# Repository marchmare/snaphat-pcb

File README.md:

# 🌻 SnapHAT - PCB design

SnapHAT is an addon for RaspberryPi Zero 2 W serving as a handheld photo camera device.

This repository contains KiCad 9 design files for the PCBs of the SnapHAT device (rev.1.1).
The boards' layout is prepared to be compatible with JLCPCB standard 2-layer PCB quote.

> [!WARNING] 
> This repository is work in progress — core features are functional, but the PCB for this device is still evolving and some parts of the design are not yet behaving as I hoped.
> To avoid unnecessary hardware headaches, check [Troubleshooting and required reworks](#troubleshooting-and-required-reworks) section!

> [!TIP] 
> Python-based app for this camera can be found in **[this repository](https://github.com/marchmare/snaphat-sw)**.

### Table of contents:

* [Features](#features)
* [Repository structure](#repository-structure)
* [Bill of Materials](#bill-of-materials)
* [Wire harnesses](#wire-harnesses)
* [RaspberryPi header connection map](#raspberrypi-header-connection-map)
* [Troubleshooting and required reworks](#troubleshooting-and-required-reworks)

## Features

* 40-pin Raspberry Pi GPIO header for integration with RaspberryPi Zero 2 W
* 8-pin PH connector and mounting support for 320x240 Waveshare 18366 2.4" LCD TFT display
* Usable with ZeroCam OV5647 5MPx wide-angled 120° camera modules or same form-factor alternatives
* <del>1200mAh Li-Po battery support (30x40mm cell footprint, 2 pin PH connector), on-board battery charging (MCP73871) and power monitoring (INA219)</del>
* USB-C charging and OTG connector for RaspberryPi SD card access (USB 2.0)
* USB OTG pogo-pin breakout board as Raspberry Pi HAT, accessing USB singals through pogo-pins, connected to main board via 4pin FFC cable
* 8 tactile user interface buttons (navigation and shutter)
* LIS2DW12 motion sensor for providing image orientation metadata
* passive buzzer for audio feedback
* exposed debug UART pins
* flower testpads, because joy and whimsy is in demand

## Repository structure

```
.
├─ main_board/
│   ├─ docs/
│   ├─ *.kicad_pro, *.kicad_sch, *.kicad_pcb
│   └─ README.md
├─ usb_hat/
│   ├─ docs/
│   ├─ *.kicad_pro, *.kicad_sch, *.kicad_pcb
│   └─ README.md
├─ img/
└─README.md
```

This repository contains two KiCad projects for each board:

* [**main_board**](main_board/) - SnapHAT main board with RaspberryPi socket connector and all camera device peripherals
* [**USB HAT**](usb_hat/) - USB OTG pogo-pin breakout board

Each board directory contains:

* `*.kicad_pro`, `*.kicad_sch`, `*.kicad_pcb` - KiCad 9 design files
* `docs/` - documentation outputs generated from the KiCad files - you will find BOM in CSV format and schematic PDF in there

In the root directory:
* `img/` - rendered previews of the boards and other images used by READMEs

## Bill of Materials

You can find BOMs for each board as CSV file in their respective `docs/` directories.
BOMs list PCB components, wire harness components, fasteners as well as OTS modules required to assemble the whole device. 

While designing SnapHAT, Farnell and TME were mostly taken into consideration as part vendors, however some parts need to be sourced from elsewhere (this applies mostly to OTS modules). 

Estimated component cost of the whole device is approximately 114 USD.

## Wire harnesses

### Display wire harness

To connect the Waveshare 18366 2.4" LCD TFT Display, use an 8-pin JST-PH (2.0 mm pitch) wire harness.
**This is not a straight-through cable — pin numbering is reversed between connectors.**

Part numbers for building the harness are listed in the main board's BOM and appear in its KiCad schematics as well.

#### Pin mapping:

| SnapHAT J1 | Signal      | LCD PH connector |
|------------|-------------|------------------|
| 1          | `3V3 (VCC)` | 8                |
| 2          | `GND`       | 7                |
| 3          | `MOSI (DIN)`| 6                |
| 4          | `SCLK (CLK)`| 5                |
| 5          | `SPI_CS`    | 4                |
| 6          | `DC`        | 3                |
| 7          | `RST`       | 2                |
| 8          | `BL`        | 1                |

### USB HAT FFC cable

To connect SnapHAT's USB HAT, use 4 core (1.0 mm pitch) >50 mm FFC cable, with **opposite sided contacts**. Proposed part number for this cable is listed in the USB HAT's BOM and appear in its KiCad schematics as well.

SnapHAT and USB HAT both include FFC connectors with top-side contacts (SnapHAT: J6, USB HAT: J1). When plugged in, FFC stiffener should face the PCB on both ends.

#### Pin mapping:

| SnapHAT J6 | Signal        | USB HAT J1 |
|------------|---------------|------------|
| 1          | `VBUS`        | 1          |
| 2          | `USBC_DATA_N` | 2          |
| 3          | `USBC_DATA_P` | 3          |
| 4          | `GND`         | 4          |

## RaspberryPi header connection map

Below table describes connected RaspberryPi GPIO pins and their intended function.

| Pin function              | Signal name        | GPIO (BCM) | Pin    | Pin    | GPIO (BCM) | Signal name      | Pin function                   | 
| ------------------------- | ------------------ | ---------- | ------ | ------ | ---------- | ---------------- | ------------------------------ |
| 3.3V power rail           | `+3V3`             | -          | **1**  | **2**  | -          | `+5V0`           | 5V power rail                  |
| I2C data                  | `I2C_SDA`          | 2          | **3**  | **4**  | -          | `+5V0`           | 5V power rail                  |
| I2C clock                 | `I2C_SCL`          | 3          | **5**  | **6**  | -          | `GND`            | Ground                         |
| _Not connected_           | -                  | 4          | **7**  | **8**  | 14         | `RPI_UART_TX`    | Debug UART Transmit          |
| Ground                    | `GND`              | -          | **9**  | **10** | 15         | `RPI_UART_RX`    | Debug UART Receive             |
| Menu button               | `BTN_MENU`         | 17         | **11** | **12** | 18         | `BUZZER_SIGNAL`  | Buzzer PWM                     |
| A button                  | `BTN_A`            | 27         | **13** | **14** | -          | `GND`            | Ground                         |
| B button                  | `BTN_B`            | 22         | **15** | **16** | 23         | -                | _Not connected_                |
| 3.3V power rail           | `+3V3`             | -          | **17** | **18** | 24         | `DISPLAY_RST`    | Display reset                  |
| Display SPI MOSI          | `DISPLAY_MOSI`     | 10         | **19** | **20** | -          | `GND`            | Ground                         |
| _Not connected_           | -                  | 9          | **21** | **22** | 25         | `DISPLAY_DC`     | Display Data/Command         |
| Display SPI serial clock  | `DISPLAY_SPI_SCLK` | 11         | **23** | **24** | 8          | `DISPLAY_SPI_CS` | Display SPI chip select        |
| Ground                    | `GND`              | -          | **25** | **26** | 7          | -                | _Not connected_                |
| Down button               | `BTN_D`            | 0          | **27** | **28** | 1          | -                | _Not connected_                |
| Left button               | `BTN_L`            | 5          | **29** | **30** | -          | `GND`            | Ground                         |
| Right button              | `BTN_R`            | 6          | **31** | **32** | 12         | `DISPLAY_BL`     | Display backlight PWM          |
| Up button                 | `BTN_U`            | 13         | **33** | **34** | -          | `GND`            | Ground                         |
| Low battery indicator LED | `LED_LBO`          | 19         | **35** | **36** | 16         | `LED_SHUTTER`    | Shutter activity LED indicator |
| Shutter button            | `BTN_SHUTTER`      | 26         | **37** | **38** | 20         | `ACCEL_INT1`     | Motion sensor interrupt 1      |
| Ground                    | `GND`              | -          | **39** | **40** | 21         | `ACCEL_INT2`     | Motion sensor interrupt 2      |

## Troubleshooting and required reworks

This revision's battery circuit (protection, charger and 5V boost) is still botched. Aside from this, SnapHAT is operational if powered by an external stable 5V supply like PC USB port or powerbank.

To make SnapHAT work in this case, simply connect VBUS to 5V0 (you can solder a wire between corresponding testpads). Keep the SW9 switch off to disable the battery charger circuit and prevent charging indicators flickering.

If you wish to dwell deeper into what's currently wrong with this design, here are symptoms observed during bringup:

* no power sourced from battery:
    - battery protection dual MOSFET have wrong topology, skip populating battery protection components entirely and populate R22 and R23 0R resistors instead to connect battery directly to the rest of the circuit. Make sure you use battery with a PCM in this case! 
* RaspberryPi stuck in boot loop when powering from battery or weaker USB port:
    - battery charging/boost regulator circuit is still wrong in this iteration, for the time being, connect VBUS testpad with the 5V0 one
* SnapHAT gets powered from connected USB-C connector when USB HAT is installed, despite turning SW9 in off position:
    - cut the VBUS trace going to J6 pin 1

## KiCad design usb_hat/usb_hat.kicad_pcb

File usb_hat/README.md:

# SnapHAT USB HAT

This directory contains design files and documentation for SnapHAT USB HAT.

## Directory structure

```
.
└─ usb_hat/
   ├─ docs/
   │    ├─ *_bom.csv
   │    └─ *_schematic.pdf
   ├─ *.kicad_pro, *.kicad_sch, *.kicad_pcb
   └─ README.md
```

## Board previews

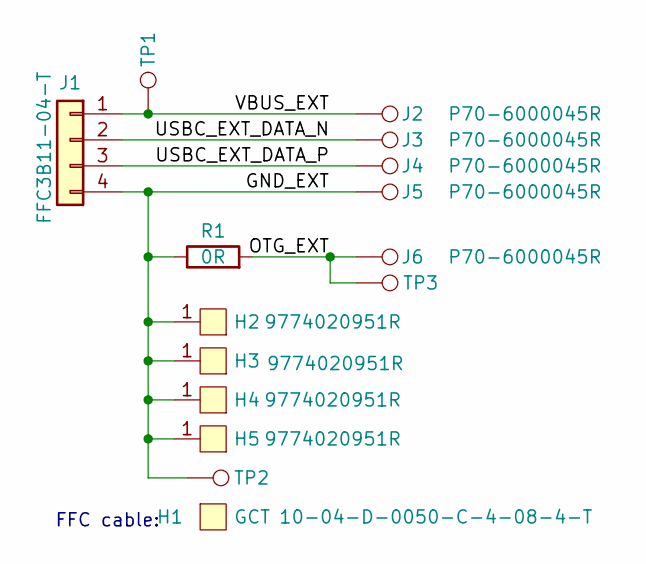
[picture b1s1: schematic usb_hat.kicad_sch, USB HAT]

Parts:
H1: 10-04-D-0050-C-4-08-4-T; Part number 10-04-D-0050-C-4-08-4-T
H2, H3, H4, H5: 9774020951R; Mounting_Wuerth_WA-SMST-2.7mm_H2mm_9774020951; Part number 9774020951R
J1: Conn_01x04_FFC3B11-04-T; GCT_FFC3B11-04-T; Part number FFC3B11-04-T
J2, J3, J4, J5, J6: P70-6000045R; HARWIN_P70-6000045R; Part number P70-6000045R
R1: 0R; R_0402_1005Metric; Part number RC0402JR-070RL
TP1, TP2, TP3: TestPoint; TestPoint_Pad_D1.5mm

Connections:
/GND_EXT: H2.1, H3.1, H4.1, H5.1, J1.4, J5.1, R1.1, TP2.1
/OTG_EXT: J6.1, R1.2, TP3.1
/USBC_EXT_DATA_N: J1.2, J3.1
/USBC_EXT_DATA_P: J1.3, J4.1
/VBUS_EXT: J1.1, J2.1, TP1.1

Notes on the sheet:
FFC cable:

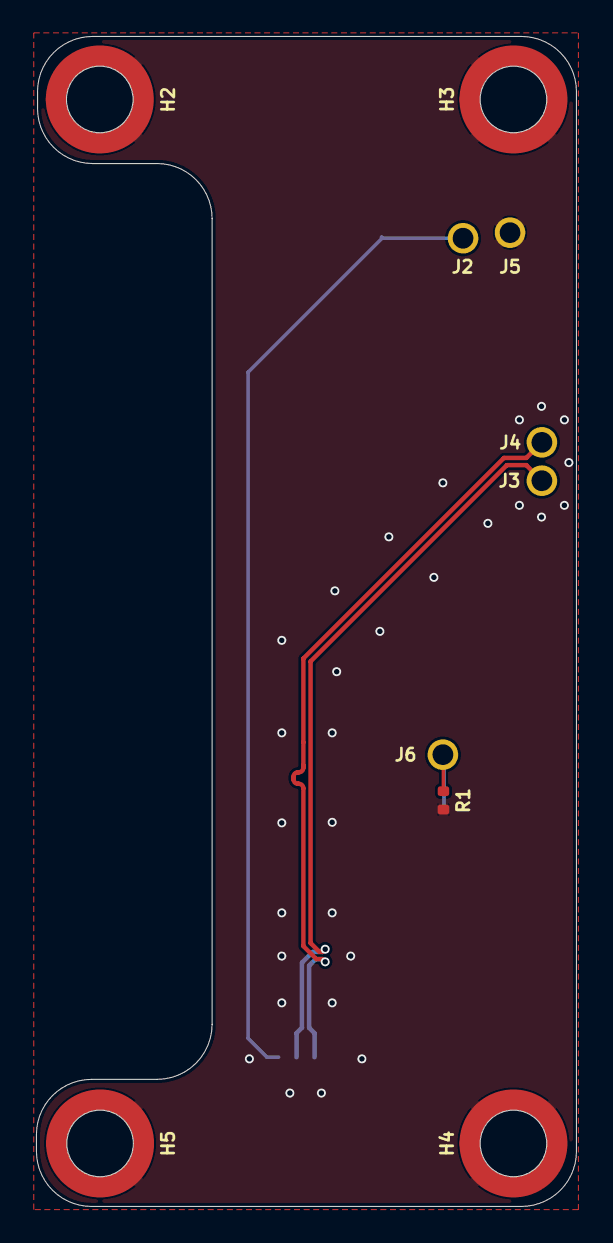
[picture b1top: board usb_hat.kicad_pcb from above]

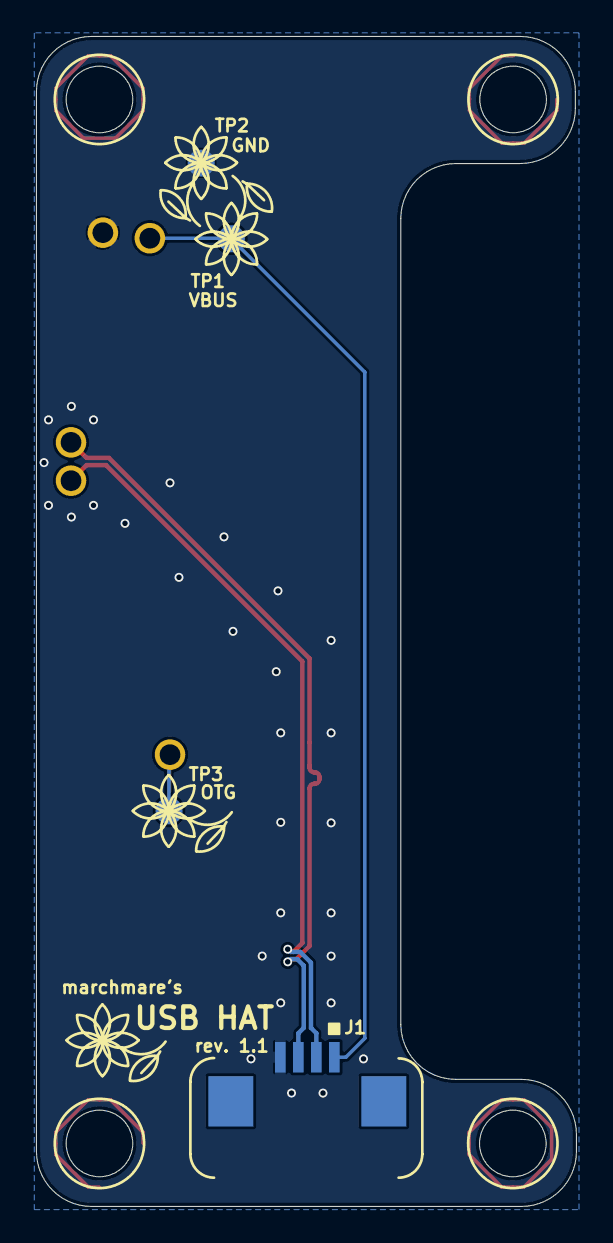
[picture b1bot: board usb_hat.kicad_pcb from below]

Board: 2 copper layers, 30.0 x 65.0 mm, 14 parts (4 on the bottom side), 5 nets.

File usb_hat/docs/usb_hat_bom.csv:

"Reference","Qty","Value","Manufacturer","Part number","SKU","Category"
"H2,H3,H4,H5","4","9774020951R","Würth Elektronik","9774020951R","",""
"J1","1","Conn_01x04_FFC3B11-04-T","GCT","FFC3B11-04-T","",""
"J2,J3,J4,J5,J6","5","P70-6000045R","Harwin","P70-6000045R","",""
"R1","1","0R","YAGEO","RC0402JR-070RL","",""
"H1","1","10-04-D-0050-C-4-08-4-T","GCT","10-04-D-0050-C-4-08-4-T ","","Wire harness"

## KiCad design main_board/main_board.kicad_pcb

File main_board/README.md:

# SnapHAT main board

This directory contains design files and documentation for SnapHAT main board.

## Directory structure

```
.
└─ main_board/
   ├─ docs/
   │    ├─ *_bom.csv
   │    └─ *_schematic.pdf
   ├─ *.kicad_pro, *.kicad_sch, *.kicad_pcb
   └─ README.md
```

## Board previews

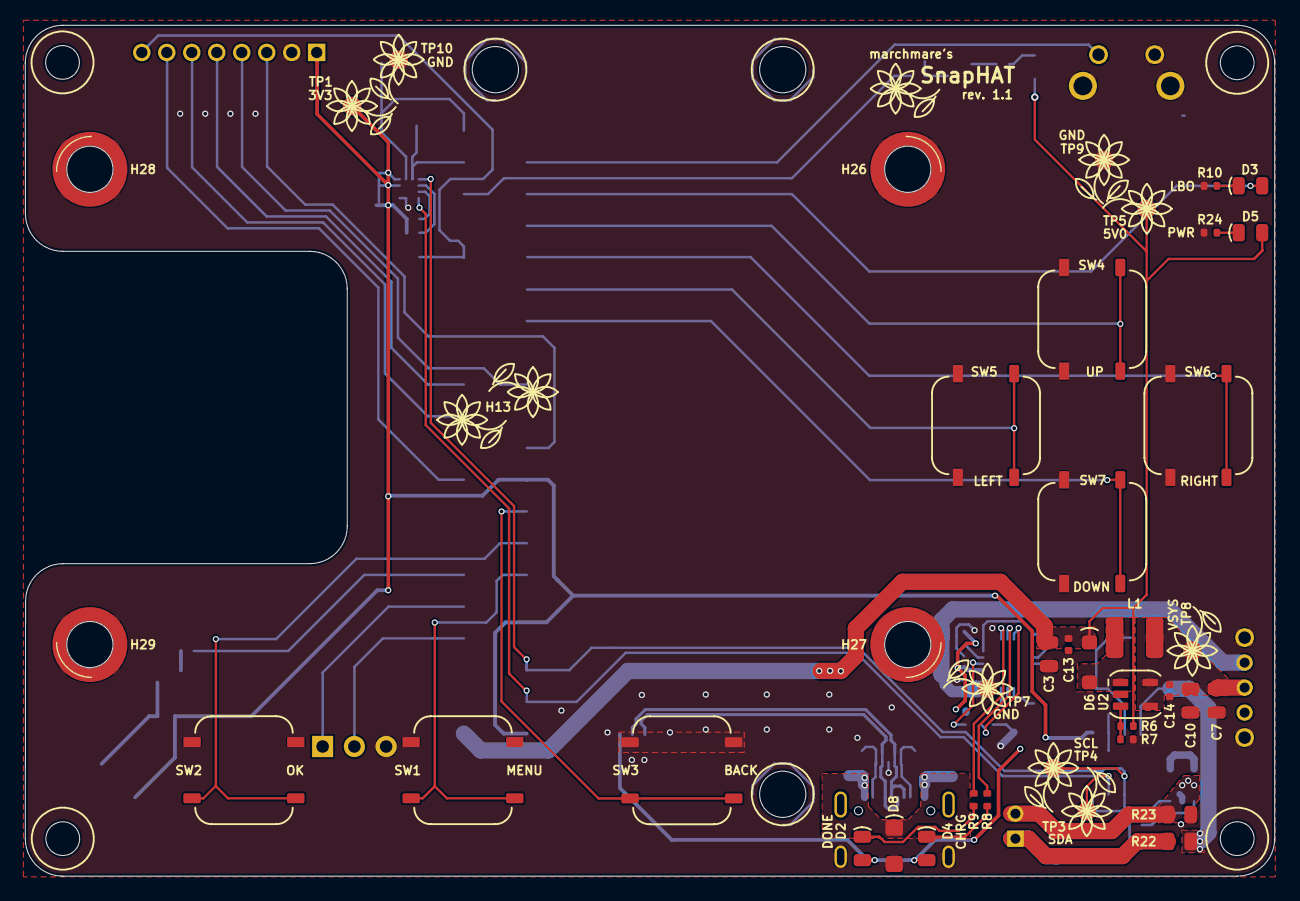
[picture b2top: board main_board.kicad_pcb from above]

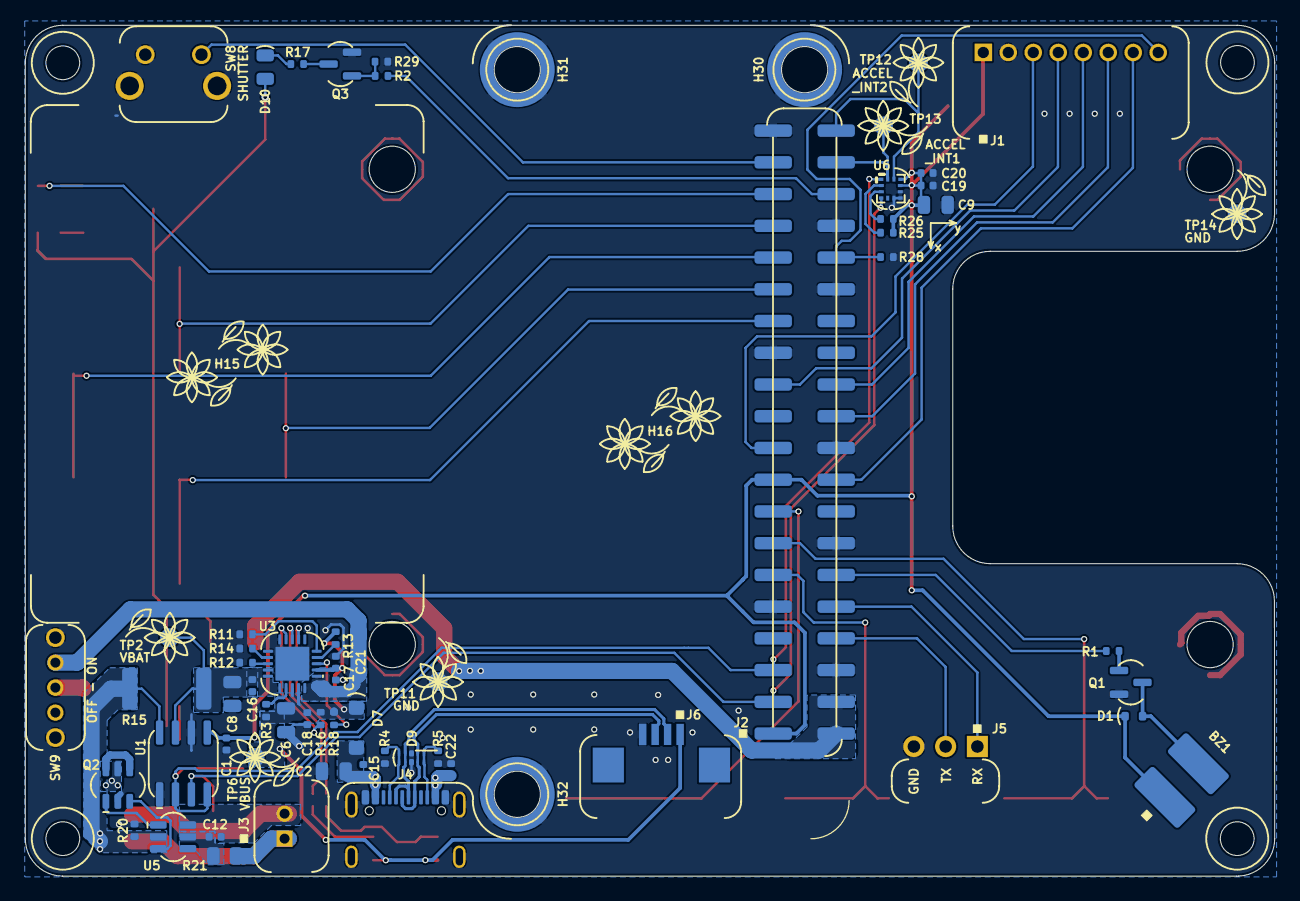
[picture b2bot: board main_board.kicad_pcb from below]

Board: 2 copper layers, 100.0 x 68.1 mm, 109 parts (64 on the bottom side), 64 nets.

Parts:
BZ1: KSSGL4B12-S; XDCR_KSSGL4B12-S
C1, C12, C13, C14, C15, C16, C17, C18, C19, C20, C21, C22: 100n; C_0402_1005Metric
C2: 22u; C_0805_2012Metric
C3: 2u2; C_0805_2012Metric
C6, C9, C10: 10u; C_0805_2012Metric
C7, C8: 4u7; C_0805_2012Metric
D1: 1N4148WT; D_SOD-523
D2, D5, D10: 0805 B LED; LED_0805_2012Metric
D3, D4: 0805 R LED; LED_0805_2012Metric
D6, D7: SL04-E3-08; DO-219AB
D8: D_SMBJ5.0A; SOD-123FL
D9: SP1004U-ULC-04UTG; SP1004UULC04UTG
H13: 18366
H15: 10304; Li-Pol_battery_8x30x40mm
H16: Raspberry Pi Zero 2 W; Raspberry_Pi_Zero_Socketed_THT_FaceDown_MountingHoles
H26, H27, H28, H29: 9774030151R; Mounting_Wuerth_WA-SMSI-M2.5_H3mm_9774030151R
H30, H31, H32: 9774100151R; Mounting_Wuerth_WA-SMSI-M2.5_H10mm_9774100151R
H33, H38, H39, H51: MountingHole; MountingHole_2.7mm
J1: Conn_01x08_S8B-PH-K-S(LF)(SN); JST_S8B-PH-K-S_LF__SN_
J2: Conn_02x20_2214SM-40G-75-PCR; PinSocket_2x20_P2.54mm_Vertical_SMD
J3: Conn_01x02_B2B-PH-K-S(LF)(SN); JST_B2B-PH-K-S_LF__SN_
J4: USB_C_USB4930-00-A; USB_C_Receptacle_GCT_USB4105-xx-A_16P_TopMnt_Horizontal
J5: Conn_01x03_MC34747; PinHeader_1x03_P2.54mm_Horizontal
J6: Conn_01x04_FFC3B11-04-T; GCT_FFC3B11-04-T
L1: L_LQH44PH100MPRL; L_LPH44PH
Q1, Q3: Q_BC817-25; SOT-23
Q2: Q_FDC6561AN; SSOT-6
R1, R2, R12: 1k; R_0402_1005Metric
R3, R11, R13, R16, R18, R25, R26: 10k; R_0402_1005Metric
R4, R5: 5k1; R_0402_1005Metric
R6: 100k; R_0402_1005Metric
R7: 33k; R_0402_1005Metric
R8, R9, R17, R24: 100R; R_0402_1005Metric
R10: 47R; R_0402_1005Metric
R14, R20: 2k7; R_0402_1005Metric
R15: 0R01; R_2512_6332Metric
R21: 330R; R_0805_2012Metric
R22, R23: 0R; R_0805_2012Metric
R28, R29: 330R; R_0402_1005Metric
SW1, SW2, SW3, SW4, SW5, SW6, SW7: SW_B3FS-1050; SW_B3FS-105xx
SW8: SW_B3F-3150
SW9: 1825232-1
TP1, TP2, TP3, TP4, TP5, TP6, TP7, TP8, TP9, TP10, TP11, TP12, TP13, TP14: TestPoint; TestPoint_Pad_D1.5mm
U1: INA219BIDR; SOIC-8_3.9x4.9mm_P1.27mm
U2: MIC2250-1YD5-TR; TSOT-23-5
U3: MCP73871T-2CCI/ML; QFN-20-1EP_4x4mm_P0.5mm_EP2.7x2.7mm
U5: AP9101CAK6-ABTRG1; SOT-26
U6: LIS2DW12TR; LGA12R50P4X4_200X200X70

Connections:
+3.3V: BZ1.1 (+), C1.1, C9.1, C19.1, C20.1, D1.1 (K), J1.1, J2.1, J2.17, R25.2, R26.2, TP1.1, U1.5 (VS), U6.9 (VDD), U6.10 (VDD_IO)
+5V: C3.1, C13.2, D5.2 (A), D6.1 (K), D10.2 (A), J2.2, J2.4, R6.1, TP5.1
/ACCEL_INT1: J2.38, TP13.1, U6.12 (INT1)
/ACCEL_INT2: J2.40, TP12.1, U6.11 (INT2)
/BTN_A: J2.13, SW2.1, SW2.2
/BTN_B: J2.15, SW3.1, SW3.2
/BTN_D: J2.27, SW7.1, SW7.2
/BTN_L: J2.29, SW5.1, SW5.2
/BTN_MENU: J2.11, SW1.1, SW1.2
/BTN_R: J2.31, SW6.1, SW6.2
/BTN_SHUTTER: J2.37, SW8.1
/BTN_U: J2.33, SW4.1, SW4.2
/BUZZER_SIGNAL: J2.12, R1.1
/CHRG_DONE_STAT: R9.1, U3.7 (STAT2)
/CHRG_STAT: R8.1, U3.8 (STAT1/~LBO)
/DISPLAY_BL: J1.8, J2.32, R28.1
/DISPLAY_DC: J1.6, J2.22
/DISPLAY_MOSI: J1.3, J2.19
/DISPLAY_RST: J1.7, J2.18
/DISPLAY_SPI_CS: J1.5, J2.24
/DISPLAY_SPI_SCLK: J1.4, J2.23
/I2C_SCL: J2.5, TP4.1, U1.2 (A0), U1.4 (SCL), U6.1 (SCL/SPC)
/I2C_SDA: J2.3, TP3.1, U1.3 (SDA), U6.4 (SDA/SDI/SDO)
/LED_LBO: D3.2 (A), J2.35
/LED_SHUTTER: J2.36, R2.1
/Power supply and LEDs/BATTERY_P: J3.1, R21.2, R22.1
/Power supply and LEDs/PROG1: R12.1, U3.13 (PROG1)
/Power supply and LEDs/PROG2: R13.1, U3.4 (PROG2)
/Power supply and LEDs/PROG3: R14.2, U3.12 (PROG3)
/Power supply and LEDs/VOUT: C17.2, SW9.1, U3.1 (OUT), U3.20 (OUT)
/RPI_UART_RX: J2.10, J5.1
/RPI_UART_TX: J2.8, J5.2
/USBC_DATA_N: D9.2, D9.9 (NC_3), J4.A7 (D-), J4.B7 (D-), J6.2
/USBC_DATA_P: D9.4, D9.7 (NC_2), J4.A6 (D+), J4.B6 (D+), J6.3
/USBC_VBUS_IN: C2.1, C15.2, C22.2, D7.2 (A), D8.1 (A1), J4.A4 (VBUS), J4.A9 (VBUS), J4.B4 (VBUS), J4.B9 (VBUS)
GND: C1.2, C2.2, C3.2, C6.2, C7.2, C8.2, C9.2, C10.2, C13.1, C14.1, C15.1, C16.1, C17.1, C18.1, C19.2, C20.2, C21.1, C22.1, D8.2 (A2), D9.3 (GND), D9.8 (GND_2), H26.1, H27.1, H28.1, H29.1, H30.1, H31.1, H32.1, J1.2, J2.6, J2.9, J2.14, J2.20, J2.25, J2.30, J2.34, J2.39, J4.A1 (GND), J4.A12 (GND), J4.B1 (GND), J4.B12 (GND), J4.S1 (SHIELD), J5.3, J6.4, Q1.2 (E), Q2.2, Q3.2 (E), R4.1, R5.1, R7.2, R10.1, R11.1, R12.2, R14.1, R20.1, R23.2, R24.1, R28.2, R29.2, SW1.3 (K), SW1.4 (A), SW2.3 (K), SW2.4 (A), SW3.3 (K), SW3.4 (A), SW4.3 (K), SW4.4 (A), SW5.3 (K), SW5.4 (A), SW6.3 (K), SW6.4 (A), SW7.3 (K), SW7.4 (A), SW8.2, SW8.3, SW8.4, SW9.SH, TP7.1, TP9.1, TP10.1, TP11.1, TP14.1, U1.1 (A1), U1.6 (GND), U2.2 (GND), U3.10 (VSS), U3.11 (VSS), U3.21 (EP), U6.6 (GND), U6.7 (RES), U6.8 (GND)
GNDS: C12.2, J3.2, Q2.5, R23.1, U5.6 (VSS)
unnamed: BZ1.2 (-), D1.2 (A), Q1.3 (C)
unnamed: D2.1 (K), R9.2
unnamed: D3.1 (K), R10.2
unnamed: D4.1 (K), R8.2
unnamed: D5.1 (K), R24.2
unnamed: D6.2 (A), L1.2, U2.1 (SW)
unnamed: D9.5, D9.6 (NC_1), J4.B5 (CC2), R5.2
unnamed: D9.1, D9.10 (NC_4), J4.A5 (CC1), R4.2
unnamed: D10.1 (K), R17.1
unnamed: Q1.1 (B), R1.2
unnamed: Q2.4, Q2.6
unnamed: Q3.1 (B), R2.2, R29.1
unnamed: Q3.3 (C), R17.2
unnamed: R15.1, R20.2, R22.2, U1.8 (VIN+), U5.2 (VM)
unnamed: R6.2, R7.1, U2.3 (FB)
unnamed: R3.2, U3.17 (CE)
unnamed: R18.2, U3.3 (SEL)
unnamed: R11.2, U3.5 (THERM)
unnamed: R16.1, U3.9 (~TE)
unnamed: Q2.3, U5.3 (CO)
unnamed: Q2.1, U5.1 (DO)
unnamed: C12.1, R21.1, U5.5 (VDD)
unnamed: R25.1, U6.2 (CS)
unnamed: R26.1, U6.3 (SDO/SDA0)
VBAT: C8.1, C16.2, R15.2, TP2.1, U1.7 (VIN-), U3.14 (VBAT), U3.15 (VBAT), U3.16 (VBAT_SENSE)
VBUS: C6.1, C18.2, C21.2, D2.2 (A), D4.2 (A), D7.1 (K), J6.1, R3.1, R13.2, R16.2, R18.1, TP6.1, U3.2 (VPCC), U3.18 (IN), U3.19 (IN)
VSYS: C7.1, C10.1, C14.2, L1.1, SW9.2, TP8.1, U2.4 (EN/DITH), U2.5 (VIN)

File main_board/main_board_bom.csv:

"Reference","Qty","Value","Manufacturer","Part number","SKU","Category"
"BZ1","1","KSSGL4B12-S","Kingstate","KSSGL4B12-S","",""
"C1,C12,C13,C14,C15,C16,C17,C18,C19,C20,C21,C22","12","100n","YAGEO","CS0402KRX7R7BB104","",""
"C2","1","22u","YAGEO","CC0805KKX5R5BB226","",""
"C3","1","2u2","YAGEO","CC0805KKX7R6BB225","",""
"C6,C9,C10","3","10u","YAGEO","CC0805KFX7R6BB106","",""
"C7,C8","2","4u7","YAGEO","CC0805KFX7R7BB475","",""
"D1","1","1N4148WT","ONSEMI","1N4148WT","",""
"D2,D5,D10","3","0805 B LED","MULTICOMP PRO","MP008292","",""
"D3,D4","2","0805 R LED","MULTICOMP PRO","MP008293","",""
"D6,D7","2","SL04-E3-08","Vishay","SL04-E3-08","",""
"D8","1","D_SMBJ5.0A","Littelfuse","SMBJ5.0A","",""
"D9","1","SP1004U-ULC-04UTG","Littelfuse","SP1004U-ULC-04UTG","",""
"H1,H2,H3,H4,H5,H6,H7,H8","8","B32-2010","OMRON","B32-2010","",""
"H26,H27,H28,H29","4","9774030151R","Würth Elektronik","9774030151R","",""
"H30,H31,H32","3","9774100151R","Würth Elektronik","9774100151R","",""
"J1","1","Conn_01x08_S8B-PH-K-S(LF)(SN)","JST","S8B-PH-K-S(LF)(SN)","",""
"J2","1","Conn_02x20_2214SM-40G-75-PCR","MULTICOMP PRO","2214SM-40G-75-PCR","",""
"J3","1","Conn_01x02_B2B-PH-K-S(LF)(SN)","JST","B2B-PH-K-S(LF)(SN)","",""
"J4","1","USB_C_USB4930-00-A","GCT","USB4930-00-A","",""
"J5","1","Conn_01x03_MC34747","MULTICOMP PRO","MC34747","",""
"J6","1","Conn_01x04_FFC3B11-04-T","GCT","FFC3B11-04-T","",""
"L1","1","L_LQH44PH100MPRL","Murata","LQH44PH100MPRL","",""
"Q1,Q3","2","Q_BC817-25","MULTICOMP PRO","BC817-25","",""
"Q2","1","Q_FDC6561AN","ON Semiconductor","FDC6561AN","",""
"R1,R2,R12","3","1k","YAGEO","RC0402FR-071KL","",""
"R3,R11,R13,R16,R18,R25,R26","7","10k","YAGEO","RC0402FR-0710KL","",""
"R4,R5","2","5k1","YAGEO","RC0402FR-075K1L","",""
"R6","1","100k","YAGEO","RC0402FR-07100KL","",""
"R7","1","33k","YAGEO","RC0402FR-0733KL","",""
"R8,R9,R17,R24","4","100R","YAGEO","RC0402JR-07100RL","",""
"R10","1","47R","YAGEO","RC0402JR-0747RL","",""
"R14,R20","2","2k7","YAGEO","RC0402FR-072K7L","",""
"R15","1","0R01","YAGEO","RL2512FK-070R01L","",""
"R21","1","330R","YAGEO","RC0805FR-07330RL","",""
"R22,R23","2","0R","YAGEO","RC0805JR-070RL","",""
"R28,R29","2","330R","YAGEO","RC0402FR-07330RL","",""
"SW1,SW2,SW3,SW4,SW5,SW6,SW7","7","SW_B3FS-1050","OMRON","B3FS-1050","",""
"SW8","1","SW_B3F-3150","OMRON","B3F-3150","",""
"SW9","1","1825232-1","TE Connectivity","1825232-1","",""
"U1","1","INA219BIDR","Texas Instruments","INA219BIDR","",""
"U2","1","MIC2250-1YD5-TR","Microchip Technology","MIC2250-1YD5-TR","",""
"U3","1","MCP73871T-2CCI/ML","Microchip Technology","MCP73871T-2CCI/ML","",""
"U5","1","AP9101CAK6-ABTRG1","Diodes Inc.","AP9101CAK6-ABTRG1","",""
"U6","1","LIS2DW12TR","STMicroelectronics","LIS2DW12TR","",""
"H9,H10,H11,H12","4","1386735","BOSSARD","1386735","","Fasteners"
"H34,H35,H36,H37","4","M2.5x4","BOSSARD","1250396","","Fasteners"
"H40,H41,H42,H43","4","M2.5x8","BOSSARD","1250434","","Fasteners"
"H44,H45,H46,H47","4","M2.5x12","BOSSARD","1538543","","Fasteners"
"H53","1","M2.5 nut","BOSSARD","1088254","","Fasteners"
"H13","1","18366","Waveshare","18366","","OTS"
"H14","1","ODS105","Odseven","ODS105","","OTS"
"H15","1","10304","","10304","","OTS"
"H16","1","Raspberry Pi Zero 2 W","Raspberry Pi","SC1176","","OTS"
"H17,H18","2","PHR-8","JST","PHR-8","","Wire harness"
"H19,H20,H21,H22,H23,H24,H25,H52","8","01SPHSPH-26L-150","JST","01SPHSPH-26L-150","","Wire harness"
"H48,H49","2","SPH-002T-P0.5S","JST","SPH-002T-P0.5S","","Wire harness"
"H50","1","PHR-2","JST","PHR-2","","Wire harness"

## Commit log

2026-03-19 Add design files, README, bom and schematic
2026-03-19 Add .gitignore
2026-03-19 Replace boost regulator with MIC2250-1YD5-TR
2026-03-19 Add display backlight pulldown
2026-03-19 Update slide switch reference to SW
2026-03-19 Replace Q2 and Q3 with FDC6561AN
2026-03-20 Add USB OTG
2026-03-22 Move power supply block to separate sheet, bringup fixes
2026-03-22 Fix BC817-25 symbol (wrong pinout)
2026-03-22 Update spacers
2026-03-22 Fix B3F-3150 symbol
2026-03-22 Fixes to power charger, cleanup schematic
2026-04-06 Add LICENSE
2026-04-09 Start updating PCB, library fixes
2026-04-10 Rerouted power and USB
2026-04-11 Fix RPi connector on schematic, route rest of signals
2026-04-11 Layout nits, add proper mounting holes
2026-04-11 Zone fixes
2026-04-11 Fix initial DRC problems, add draft USB hat
2026-04-12 Route USB hat
2026-04-12 Layout nits
2026-04-12 Arrange designators, clear DRC, cleanups
2026-04-12 Add FFC cable info
2026-04-12 Fixes to library, add updated schematic PDF and BOM
2026-04-13 Add LED_SHUTTER
2026-04-13 Replace FFC connector with 1mm pitch
2026-04-14 Reroute USB, add shutter LED signal pulldown
2026-04-14 Update README and docs
2026-04-16 Move main board to separate project
2026-04-16 Move USB HAT to separate project
2026-04-16 Clear root dir
2026-04-16 Fix differential pair clearence in board settings and GND pour
2026-04-18 Fix P70-6000045R missing from BOM
2026-05-05 Add TODOs from rev.1.1 bringup
2026-05-06 Update README's troubleshooting section, update bringup TODOs
2026-05-09 Update README (real life photos, wire harness info), add a TODO
